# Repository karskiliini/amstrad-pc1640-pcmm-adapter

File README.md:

# amstrad-pc1640-pcmm-adapter

Video adapter for connecting an Amstrad PC1640 to an Amstrad PC-MM monochrome monitor.

The PC1640 and PC-MM were never designed to work together — the PC-MM was built for the PC1512. This project documents the signal incompatibilities and presents four adapter designs to bridge them.

## The Problem

| Issue | PC1640 output | PC-MM expects |
|-------|---------------|---------------|
| Connector | DE-9 (9-pin D-sub) | 8-pin DIN |
| Signal polarity | Normal (active-high TTL) | Inverted (active-low TTL) |
| Sync | Separate H-Sync + V-Sync | Composite Sync (combined) |
| Frequency | 21.85 kHz (EGA) / 15.7 kHz (CGA) | 15.75 kHz only |
| Power (14-pin DIN) | Same pinout | Same pinout — **compatible** |

**Solutions:** Run PC1640 in CGA mode (SW8 = OFF) for simplest adapter, or keep EGA mode (SW8 = ON) with additional signal conversion. See options below.

## Documentation

- **[Signal Analysis](docs/signal-analysis.md)** — Full pinouts, signal levels, frequency specs, and compatibility breakdown for both devices

## Adapter Options

### CGA mode (SW8 = OFF) — simpler adapter

| | Option A | Option B | Option C |
|---|---|---|---|
| **Approach** | External adapter | Monitor internal bypass | Passive test cable |
| **ICs needed** | 2 (74HC04 + 74HC86) | 1 (74HC86) | 0 |
| **Monitor mod** | No | Yes | No |
| **Image quality** | Correct | Correct | Inverted (negative) |
| **Cost** | ~15–20€ | ~12–15€ | ~5€ |
| **Difficulty** | Easy | Medium | Very easy |
| **Reversible** | Fully | Partially | Fully |
| **Recommended** | **Yes** | For advanced users | Testing only |

### [Option A: External Adapter](docs/option-a-external-adapter.md) (recommended for CGA mode)

Two ICs on a small PCB handle everything:
- **74HC04** inverts R, G, B, I, and C-Sync to match PC-MM's active-low input
- **74HC86** combines H-Sync + V-Sync into Composite Sync via XOR

No monitor modification needed. Fully reversible.

### [Option B: Monitor Internal Bypass](docs/option-b-monitor-bypass.md)

Bypass the PC-MM's internal TC74HC04 inverter, allowing standard TTL signals to pass through directly. The adapter only needs sync combining (one 74HC86). Smaller and simpler adapter PCB, but requires opening the CRT monitor.

### [Option C: Passive Test Cable](docs/option-c-passive-test.md)

Quick-and-dirty test with just two resistors and direct wiring. Image will be inverted (negative), but confirms that the signal path and frequency are compatible before committing to a PCB design.

---

### EGA mode (SW8 = ON) — preserves full EGA capability

### [Option D: EGA Mode Adapter](docs/option-d-ega-mode.md)

Keep the PC1640 in EGA mode for full 64-color palette capability. This option has two tiers:

**D1: 200-line programs (most DOS games)** — Same adapter as Option A, plus 3 Schottky diodes (or 74HC32 OR gate) to derive the Intensity signal from EGA's three secondary color lines. Works at 15.7 kHz. Cost: ~16–22€.

**D2: 350-line programs (Windows, productivity software)** — PC-MM cannot physically display 21.85 kHz. Requires an external scan rate converter:
- Budget: MCE2VGA + GBS-Control chain (~50–90€)
- Quality: OSSC Pro (~350€)

| | D1 (200-line) | D2 (350-line) |
|---|---|---|
| **Additional HW** | 3 diodes or 1 IC | Scan converter |
| **Programs** | Most DOS games | Windows, SimCity, Flight Sim |
| **H-frequency** | 15.7 kHz (native) | 21.85 kHz → 15.7 kHz (converted) |
| **Cost** | ~16–22€ | ~50–350€ + adapter |
| **Complexity** | Low | High |

## Chosen Design: Option A

Option A (external adapter, no monitor modification) is the selected approach.

### Hardware Files

- [`hardware/netlist.md`](hardware/netlist.md) — Complete point-to-point wiring with ASCII schematic
- [`hardware/bom.csv`](hardware/bom.csv) — Bill of materials with supplier part numbers
- [`hardware/amstrad-pc1640-pcmm-adapter.kicad_pro`](hardware/amstrad-pc1640-pcmm-adapter.kicad_pro) — KiCad project

## Project Status

- [x] Signal analysis and pinout research
- [x] Adapter design (schematic level)
- [x] Netlist and BOM
- [x] KiCad project skeleton
- [ ] KiCad schematic (.kicad_sch)
- [ ] PCB layout (.kicad_pcb)
- [ ] Prototype build and testing
- [ ] Gerber files for manufacturing

## References

- [Amstrad PC1640 Technical Reference Manual](https://www.seasip.info/AmstradXT/1640tech/section1.html)
- [Amstrad PC1512 Technical Reference Manual](https://www.seasip.info/AmstradXT/1512tech/section1.html)
- [PC1640 DIP Switch Settings](https://www.seasip.info/AmstradXT/pc1640dip.html)
- [PC1512 Video Inverter Circuit](https://ctrl-alt-rees.com/2018-09-25-amstrad-pc1512-video-inverter-circuit.html)
- [Amstrad Video Liberator (GitHub)](https://github.com/reeshub/amstrad-pc1512-video-liberator)
- [Necroware MCE Adapter (GitHub)](https://github.com/necroware/mce-adapter)
- [Monotech EGA-Mono-Composite-Converter (GitHub)](https://github.com/monotech/EGA-Mono-Composite-Coverter)

## License

This project is for personal use. Feel free to use and adapt for your own retro computing needs.

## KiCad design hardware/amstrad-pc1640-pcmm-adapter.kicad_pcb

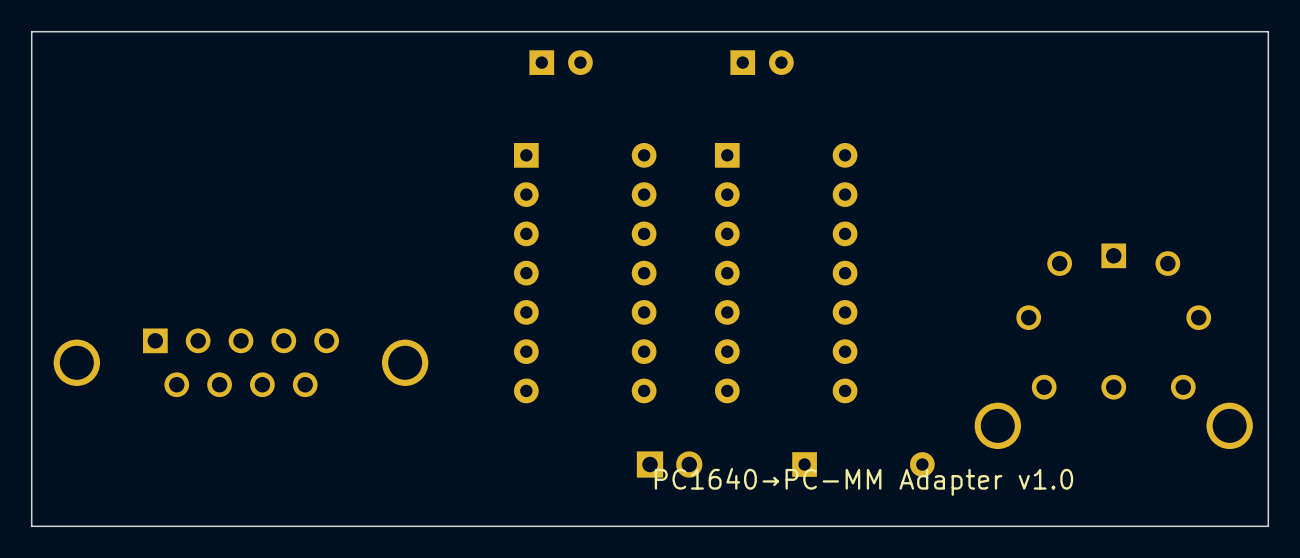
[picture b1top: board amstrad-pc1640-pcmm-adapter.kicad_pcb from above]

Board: 2 copper layers, 80.0 x 32.0 mm, 8 parts (0 on the bottom side), 15 nets, no tracks yet.

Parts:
C1, C2: 100nF; C_Disc_D5.0mm_W2.5mm_P2.50mm
J1: DB9_Male; DSUB-9_Male_Horizontal_P2.77x2.84mm
J2: DIN-8; DIN-8_Video
J3: +5V/GND; PinHeader_1x02_P2.54mm_Vertical
R1: 10k; R_Axial_DIN0207_L6.3mm_D2.5mm_P7.62mm_Horizontal
U1: 74HC04; DIP-14_W7.62mm
U2: 74HC86; DIP-14_W7.62mm

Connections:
+5V: C1.1, C2.1, J3.1, R1.1, U1.14, U2.14
BLACK: J2.4, R1.2
BLUE: J1.5, U1.5
BLUE_INV: J2.6, U1.6
CSYNC: U1.11, U2.3
CSYNC_INV: J2.1, U1.10
GND: C1.2, C2.2, J1.1, J2.3, J2.7, J2.SH1, J2.SH2, J3.2, U1.7, U1.13, U2.4, U2.5, U2.7, U2.9, U2.10, U2.12, U2.13
GREEN: J1.4, U1.3
GREEN_INV: J2.5, U1.4
HSYNC: J1.8, U2.1
INTENSITY: J1.6, U1.9
INTENSITY_INV: J2.2, U1.8
RED: J1.3, U1.1
RED_INV: J2.8, U1.2
VSYNC: J1.9, U2.2

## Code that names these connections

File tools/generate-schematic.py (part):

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
        # Net labels for signal routing
        net_label("RED", 80, 90),
        net_label("RED_INV", 200, 90),
        net_label("GREEN", 80, 95),
        net_label("GREEN_INV", 200, 95),
        net_label("BLUE", 80, 100),
        net_label("BLUE_INV", 200, 100),
        net_label("INTENSITY", 80, 105),
        net_label("INTENSITY_INV", 200, 105),
        net_label("HSYNC", 80, 115),
        net_label("VSYNC", 80, 120),
        net_label("CSYNC", 170, 175),
        net_label("CSYNC_INV", 200, 110),
        net_label("BLACK", 230, 160),
    ])

    sch = f"""(kicad_sch
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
